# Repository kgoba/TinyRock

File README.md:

Model rocket flight computer (parachute eject and maximum altitude tracking)

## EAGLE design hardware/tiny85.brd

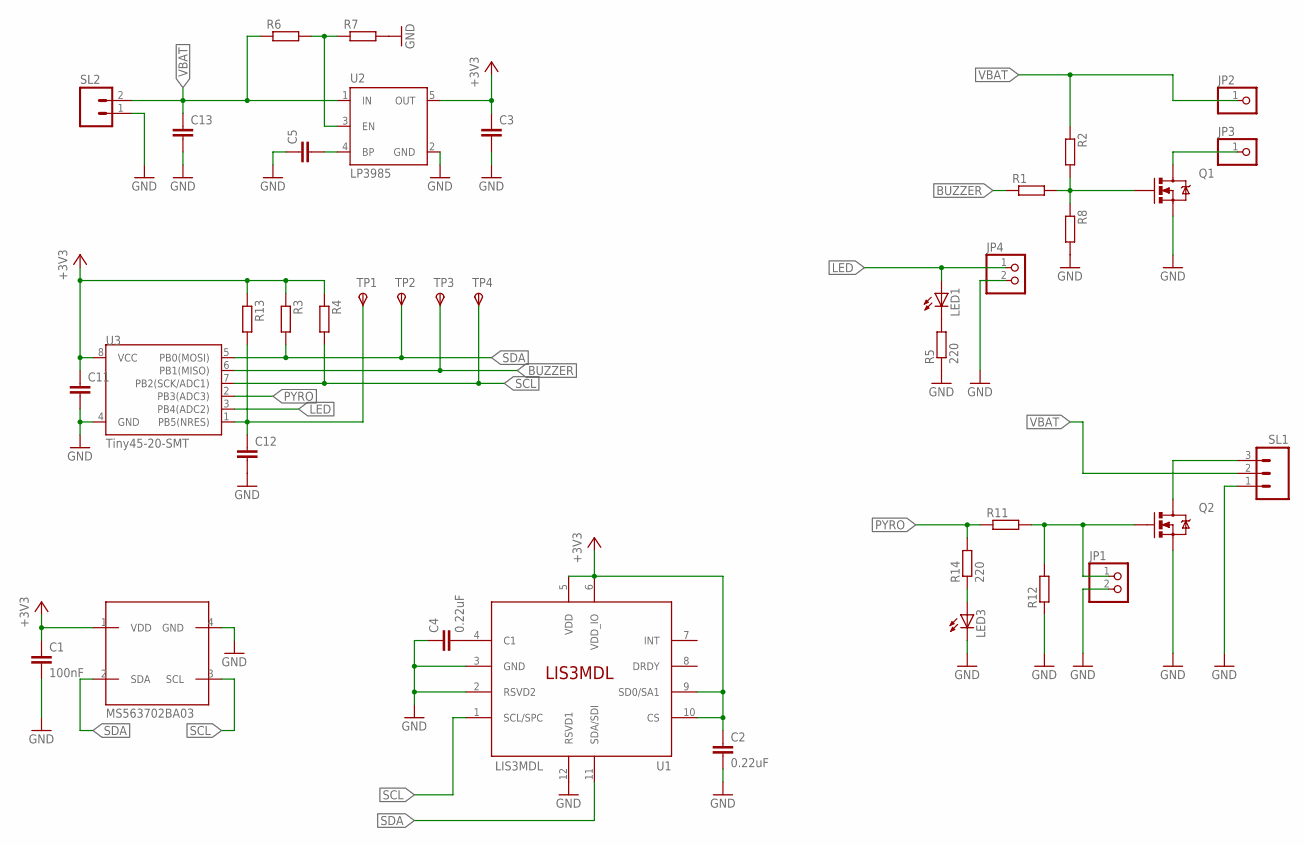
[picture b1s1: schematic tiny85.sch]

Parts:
C1: 100nF; C0603
C2, C4: 0.22uF; C0603K
C3, C5, C11, C12, C13: C-EUC0603; C0603
IC1: MS563702BA03; MS5637
JP1, JP4: PINHD-1X2; 1X02
JP2, JP3: PINHD-1X1; 1X01
LED1, LED3: LEDCHIPLED_0805; CHIPLED_0805
Q1, Q2: MOSFET-NCHANNELBSS123LT1G; SOT23-3
R1, R2, R3, R4, R6, R7, R8, R11, R12, R13: R-EU_R0603; R0603
R5, R14: 220; R0603
SL1: M03; 03P
SL2: M02; 02P
TP1, TP2, TP3, TP4: TPSB1,27; B1,27
U1: LIS3MDL; VFLGA-12
U2: LP3985; SOT23-5
U3: Tiny45-20-SMT; SO08-EIAJ

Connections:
+3V3: C1.1, C2.1, C3.1, C11.1, IC1.1 (VDD), R3.1, R4.1, R13.1, U1.5 (VDD), U1.6 (VDD_IO), U1.9 (SD0/SA1), U1.10 (CS), U2.5 (OUT), U3.8 (VCC)
BUZZER: R1.1, TP3.TP, U3.6 (PB1(MISO))
GND: C1.2, C2.2, C3.2, C4.1, C5.1, C11.2, C12.2, C13.2, IC1.4 (GND), JP1.2, JP4.2, LED3.C, Q1.2 (S), Q2.2 (S), R5.1, R7.2, R8.2, R12.1, SL1.1, SL2.1, U1.2 (RSVD2), U1.3 (GND), U1.12 (RSVD1), U2.2 (GND), U3.4 (GND)
LED: JP4.1, LED1.A, U3.3 (PB4(ADC2))
unnamed: JP3.1, Q1.3 (D)
unnamed: C5.2, U2.4 (BP)
unnamed: Q1.1 (G), R1.2, R2.2, R8.1
unnamed: LED1.C, R5.2
unnamed: C4.2, U1.4 (C1)
unnamed: R6.2, R7.1, U2.3 (EN)
unnamed: Q2.3 (D), SL1.3
unnamed: C12.1, R13.2, TP1.TP, U3.1 (PB5(NRES))
unnamed: JP1.1, Q2.1 (G), R11.2, R12.2
unnamed: LED3.A, R14.1
PYRO: R11.1, R14.2, U3.2 (PB3(ADC3))
SCL: IC1.3 (SCL), R4.2, TP4.TP, U1.1 (SCL/SPC), U3.7 (PB2(SCK/ADC1))
SDA: IC1.2 (SDA), R3.2, TP2.TP, U1.11 (SDA/SDI), U3.5 (PB0(MOSI))
VBAT: C13.1, JP2.1, R2.1, R6.1, SL1.2, SL2.2, U2.1 (IN)

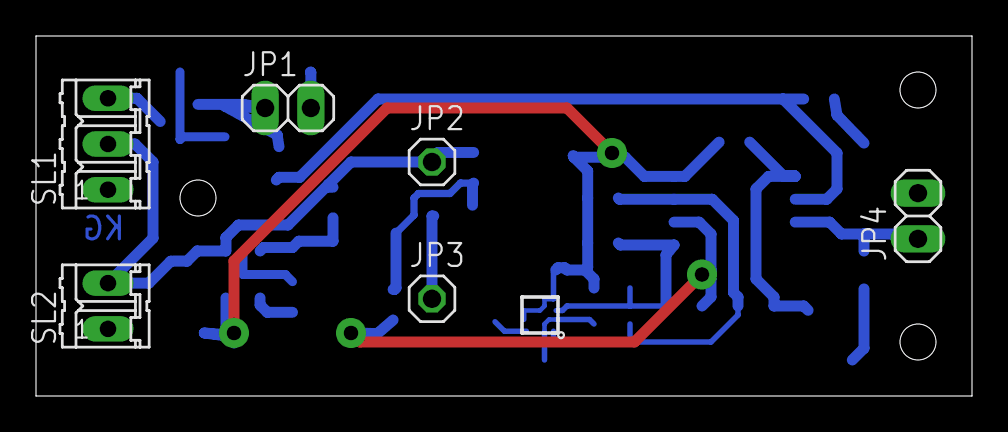
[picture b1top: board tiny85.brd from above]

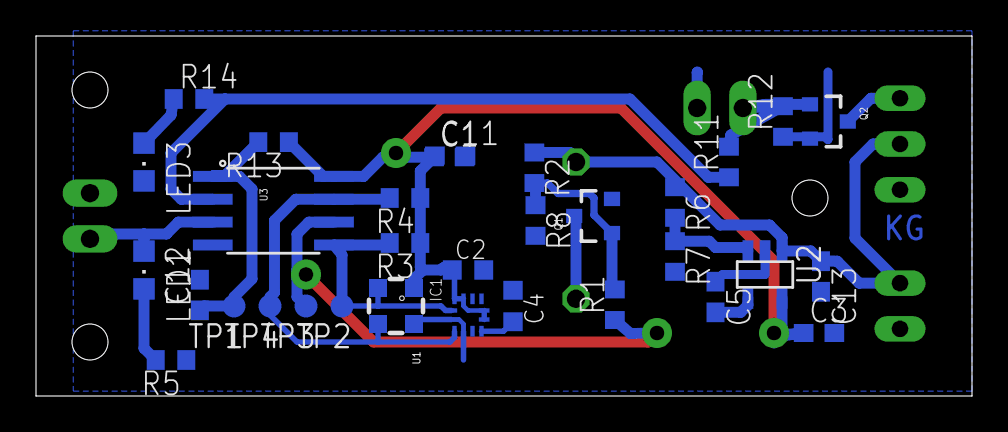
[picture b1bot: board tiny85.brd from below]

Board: 2 copper layers, 52.0 x 20.0 mm, 38 parts (32 on the bottom side), 18 nets.

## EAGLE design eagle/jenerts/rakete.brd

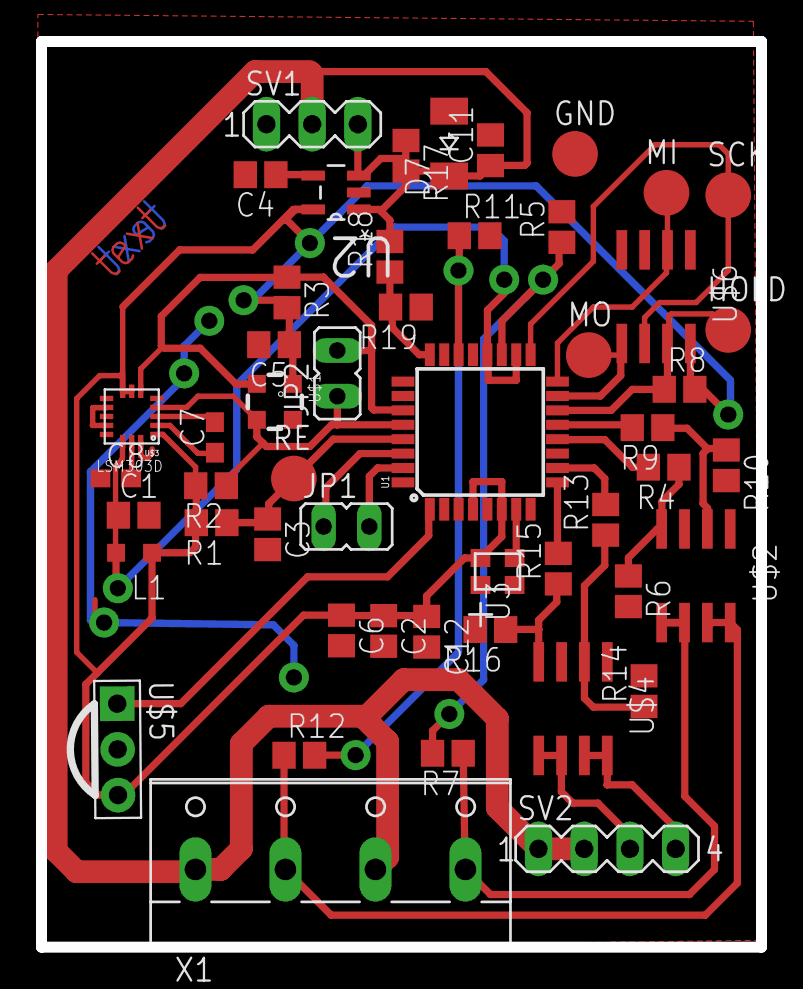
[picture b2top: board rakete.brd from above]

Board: 2 copper layers, 40.0 x 50.3 mm, 51 parts (0 on the bottom side), 35 nets.

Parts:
C1, C2, C3, C4, C5, C6, C11, C12: 0.1; C0805
C7: 0.22uF; C0603
C8: 4.7uF; C0603
D7: SOD-123_MINI-SMA
GND: TPB2,54; B2,54
HOLD: TPB2,54; B2,54
JP1, JP2: JP1
L1: L2012C
MI: TPB2,54; B2,54
MO: TPB2,54; B2,54
R1, R18, R19: 10k; R0805
R2, R3, R17: 3.3K; R0805
R4, R5, R6, R7, R8, R9, R10, R11, R12, R13, R14, R15, R16: R0805
RE: TPB2,54; B2,54
SCK: TPB2,54; B2,54
SV1: MA03-1
SV2: MA04-1
U1: ATMEGA328P_TQFP; TQFP32-08
U2: MIC5301-3.3YD5; SOT95P280X130-5N
U3: 501; SI501_4_2X2.5
U$1: MS563702BA03; MS5637
U$2, U$4: FDS6984AS; SO8
U$3: LSM303D; TFLGA16L
U$5: PNA460XM
U$6: 25FL208K0RMFI041; SO08
X1: W237-4

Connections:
+3V3: C2.1, C5.1, C6.1, C12.1, L1.1, R1.2, R2.2, R3.2, R8.2, U1.4, U1.6, U2.5, U3.4, U$1.1, U$3.P$1, U$3.P$7, U$3.P$8, U$5.3, U$6.8
A1: R18.1, R19.2, U1.24
A6: R5.1, R7.2, U1.19
A7: R11.1, R12.2, U1.22
AVCC: C1.1, L1.2, U1.18, U1.20, U$3.P$14
D0/RX: JP1.1, U1.30
D1/TX: JP1.2, U1.31
D3: U1.1, U$5.1
D5: R15.2, U1.9
D6: R13.2, U1.10
D8: R4.2, U1.12
D9: R9.2, U1.13
D10~: HOLD.TP, R8.1, U1.14, U$6.7
D11/MOSI: MO.TP, U1.15, U$6.5
D12/MISO: MI.TP, U1.16, U$6.2
D13/SCK: SCK.TP, U1.17, U$6.6
GND: C1.2, C2.2, C3.2, C4.2, C5.2, C6.2, C8.1, C11.2, C12.2, D7.A, GND.TP, R5.2, R6.2, R10.2, R11.2, R14.2, R16.2, R19.1, SV1.1, U1.3, U1.5, U1.21, U2.2, U3.2, U$1.4, U$2.1, U$2.3, U$3.P$5, U$3.P$10, U$3.P$12, U$3.P$13, U$3.P$16, U$4.1, U$4.3, U$5.2, U$6.1, U$6.3, U$6.4
unnamed: U1.7, U3.3
unnamed: R4.1, R6.1, U$2.4
unnamed: R7.1, U$2.5, U$2.6, X1.4
unnamed: C7.1, U$3.P$2
unnamed: C7.2, U$3.P$3
unnamed: C8.2, U$3.P$15
unnamed: R9.1, R10.1, U$2.2
unnamed: R12.1, U$2.7, U$2.8, X1.2
unnamed: C4.1, U2.4
unnamed: R13.1, R14.1, U$4.2
unnamed: R15.1, R16.1, U$4.4
ON: R17.1, SV1.3, U2.3
P3: SV2.4, U$4.7, U$4.8
P4: SV2.3, U$4.5, U$4.6
RES: C3.1, R1.1, RE.TP, U1.29
SCL: JP2.1, R2.1, U1.28, U$1.3, U$3.P$4
SDA: JP2.2, R3.1, U1.27, U$1.2, U$3.P$6
V+: C11.1, D7.C, R17.2, R18.2, SV1.2, SV2.1, SV2.2, U2.1, X1.1, X1.3

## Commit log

2016-10-12 Added barometer
2016-11-01 Update file locations, add OpenRocket model and GPS tracker code
2016-12-06 Updated file structure

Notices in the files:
parts and their libraries:
SparkFun-DigitalIC: Licensing: Creative Commons ShareAlike 4.0 International - https://creativecommons.org/licenses/by-sa/4.0
freetronics-original: Licensing: CC v3.0 Share-Alike You are welcome to use this library for commercial purposes.
